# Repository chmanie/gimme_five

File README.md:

# gimme_five
5V Eurorack PSU Adapter

## License

cc-by-sa-4.0

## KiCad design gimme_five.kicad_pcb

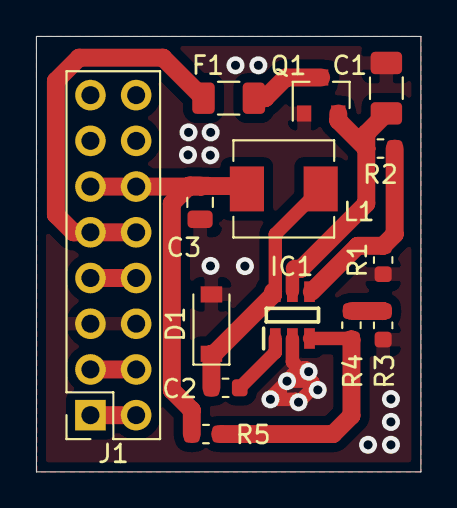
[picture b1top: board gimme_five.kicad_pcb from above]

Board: 2 copper layers, 21.4 x 24.2 mm, 14 parts (0 on the bottom side), 13 nets.

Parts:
C1: 10u; C_1206_3216Metric
C2: 10n; C_0603_1608Metric
C3: 22u; C_0805_2012Metric
D1: B5819W; D_SOD-123
F1: Polyfuse; Fuse_1206_3216Metric
IC1: MP2359DJ-LF-Z; SOT95P280X100-6N
J1: Conn_02x08_Odd_Even; PinSocket_2x08_P2.54mm_Vertical
L1: 10u; L_Sunlord_MWSA0518_5.4x5.2mm
Q1: AO3401A; SOT-23
R1: 68k; R_0603_1608Metric
R2: 100k; R_0603_1608Metric
R3: 820R; R_0603_1608Metric
R4: 10k; R_0603_1608Metric
R5: 56k; R_0603_1608Metric

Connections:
+5V: C3.1, J1.11, J1.12, L1.1, R5.2
+12V: F1.2, J1.9, J1.10
-12V: J1.1, J1.2
GND: C1.1, C3.2, D1.2, IC1.2, J1.5, J1.6, Q1.1, R1.1, R3.1
unnamed: C1.2, IC1.5, Q1.2, R2.2
unnamed: C2.1, IC1.1
unnamed: C2.2, D1.1, IC1.6, L1.2
unnamed: F1.1, Q1.3
unnamed: IC1.3, R4.2, R5.1
unnamed: IC1.4, R1.2, R2.1
unnamed: J1.3, J1.4
unnamed: J1.7, J1.8
unnamed: R3.2, R4.1

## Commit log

2020-12-28 License

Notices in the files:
gimme_five.kicad_pcb:
CC BY-SA 2.0
